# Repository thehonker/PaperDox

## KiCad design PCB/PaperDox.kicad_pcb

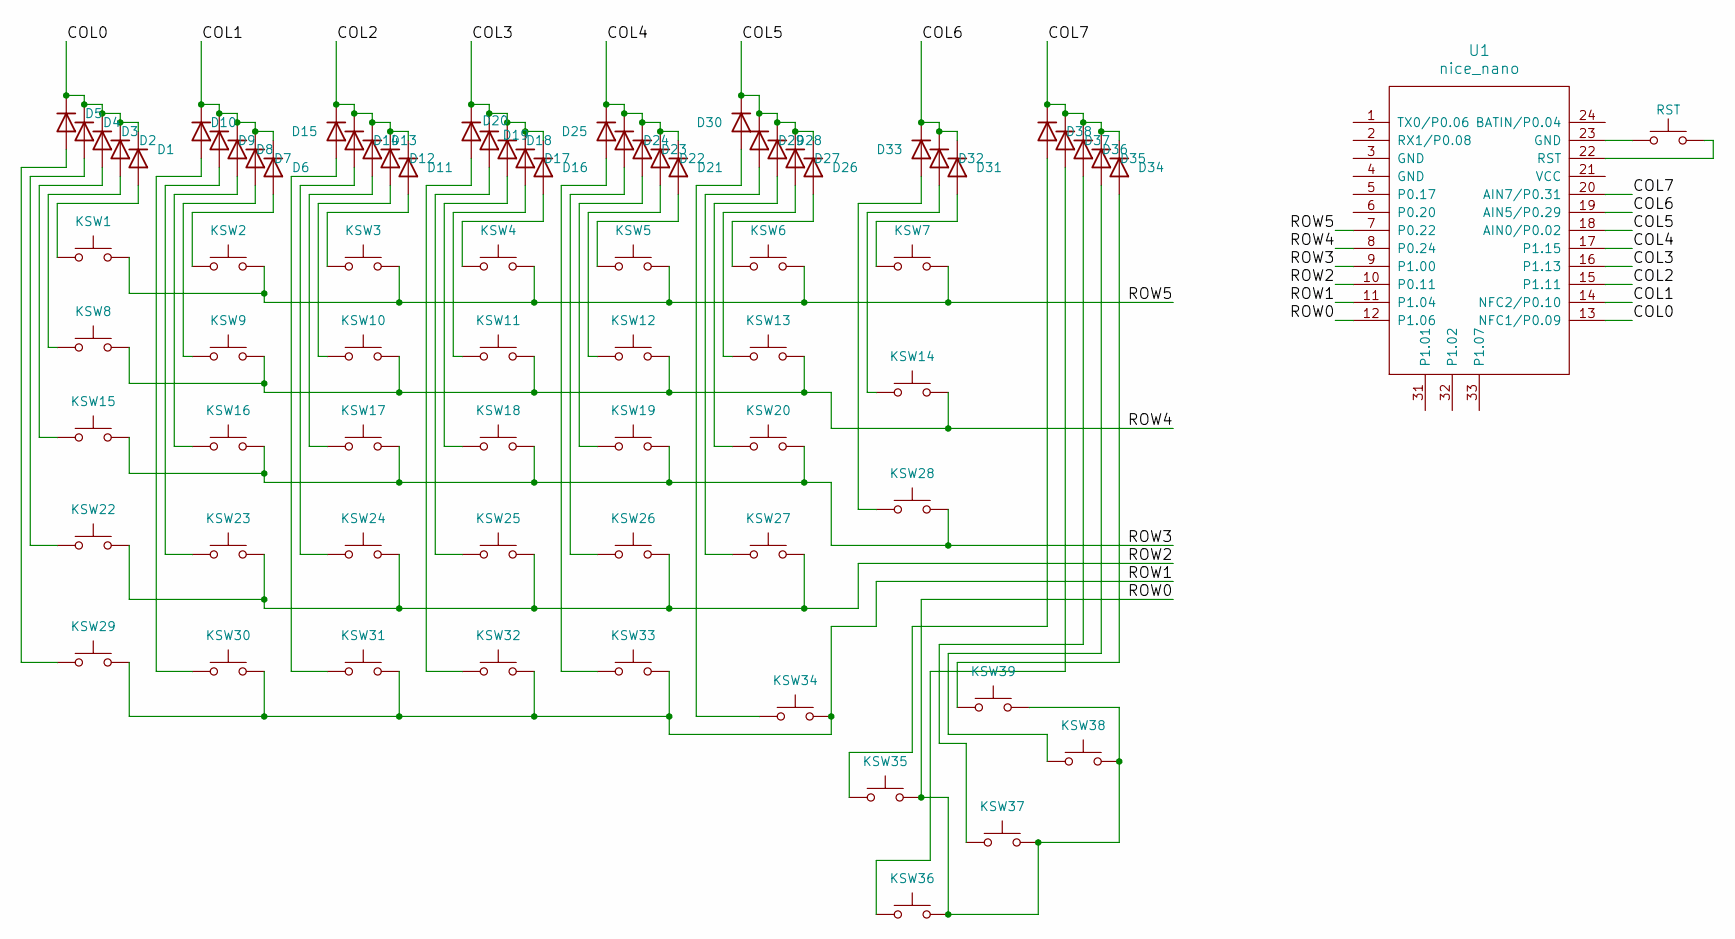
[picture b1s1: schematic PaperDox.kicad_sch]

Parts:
D1, D2, D3, D4, D5, D6, D7, D8, D9, D10, D11, D12, D13, D14, D15, D16, D17, D18, D19, D20, D21, D22, D23, D24, D25, D26, D27, D28, D29, D30, D31, D32, D33, D34, D35, D36, D37, D38: 1N4148; ComboDiode
KSW1, KSW2, KSW3, KSW4, KSW5, KSW6, KSW7, KSW8, KSW9, KSW10, KSW11, KSW12, KSW13, KSW14, KSW15, KSW16, KSW17, KSW18, KSW19, KSW20, KSW22, KSW23, KSW24, KSW25, KSW26, KSW27, KSW28, KSW29, KSW30, KSW31, KSW32, KSW33, KSW34, KSW35, KSW36, KSW37, KSW38, KSW39: Keyswitch; Choc_Hotswap
RST: SW_Push; SW_PUSH_6mm
U1: nice_nano; ProMicro_Mill-Max

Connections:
/COL0: D1.1 (K), D2.1 (K), D3.1 (K), D4.1 (K), D5.1 (K), U1.13 (NFC1/P0.09)
/COL1: D6.1 (K), D7.1 (K), D8.1 (K), D9.1 (K), D10.1 (K), U1.14 (NFC2/P0.10)
/COL2: D11.1 (K), D12.1 (K), D13.1 (K), D14.1 (K), D15.1 (K), U1.15 (P1.11)
/COL3: D16.1 (K), D17.1 (K), D18.1 (K), D19.1 (K), D20.1 (K), U1.16 (P1.13)
/COL4: D21.1 (K), D22.1 (K), D23.1 (K), D24.1 (K), D25.1 (K), U1.17 (P1.15)
/COL5: D26.1 (K), D27.1 (K), D28.1 (K), D29.1 (K), D30.1 (K), U1.18 (AIN0/P0.02)
/COL6: D31.1 (K), D32.1 (K), D33.1 (K), U1.19 (AIN5/P0.29)
/COL7: D34.1 (K), D35.1 (K), D36.1 (K), D37.1 (K), D38.1 (K), U1.20 (AIN7/P0.31); also elsewhere on the board
/ROW0: KSW35.2, KSW36.2, KSW37.2, KSW38.2, KSW39.2, U1.12 (P1.06)
/ROW1: KSW29.2, KSW30.2, KSW31.2, KSW32.2, KSW33.2, KSW34.2, U1.11 (P1.04)
/ROW2: KSW22.2, KSW23.2, KSW24.2, KSW25.2, KSW26.2, KSW27.2, U1.10 (P0.11)
/ROW3: KSW15.2, KSW16.2, KSW17.2, KSW18.2, KSW19.2, KSW20.2, KSW28.2, U1.9 (P1.00)
/ROW4: KSW8.2, KSW9.2, KSW10.2, KSW11.2, KSW12.2, KSW13.2, KSW14.2, U1.8 (P0.24)
/ROW5: KSW1.2, KSW2.2, KSW3.2, KSW4.2, KSW5.2, KSW6.2, KSW7.2, U1.7 (P0.22)
unnamed: D1.2 (A), KSW1.1
unnamed: D2.2 (A), KSW8.1
unnamed: D3.2 (A), KSW15.1
unnamed: D4.2 (A), KSW22.1
unnamed: D5.2 (A), KSW29.1
unnamed: D6.2 (A), KSW2.1
unnamed: D7.2 (A), KSW9.1
unnamed: D8.2 (A), KSW16.1
unnamed: D9.2 (A), KSW23.1
unnamed: D10.2 (A), KSW30.1
unnamed: D11.2 (A), KSW3.1
unnamed: D12.2 (A), KSW10.1
unnamed: D13.2 (A), KSW17.1
unnamed: D14.2 (A), KSW24.1
unnamed: D15.2 (A), KSW31.1
unnamed: D16.2 (A), KSW4.1
unnamed: D17.2 (A), KSW11.1
unnamed: D18.2 (A), KSW18.1
unnamed: D19.2 (A), KSW25.1
unnamed: D20.2 (A), KSW32.1
unnamed: D21.2 (A), KSW5.1
unnamed: D22.2 (A), KSW12.1
unnamed: D23.2 (A), KSW19.1
unnamed: D24.2 (A), KSW26.1
unnamed: D25.2 (A), KSW33.1
unnamed: D26.2 (A), KSW6.1
unnamed: D27.2 (A), KSW13.1
unnamed: D28.2 (A), KSW20.1
unnamed: D29.2 (A), KSW27.1
unnamed: D30.2 (A), KSW34.1
unnamed: D31.2 (A), KSW7.1
unnamed: D32.2 (A), KSW14.1
unnamed: D33.2 (A), KSW28.1
unnamed: D34.2 (A), KSW39.1
unnamed: D35.2 (A), KSW38.1
unnamed: D36.2 (A), KSW37.1
unnamed 50: RST.1, U1.23 (GND); also elsewhere on the board
unnamed 51: RST.2, U1.22 (RST); also elsewhere on the board

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
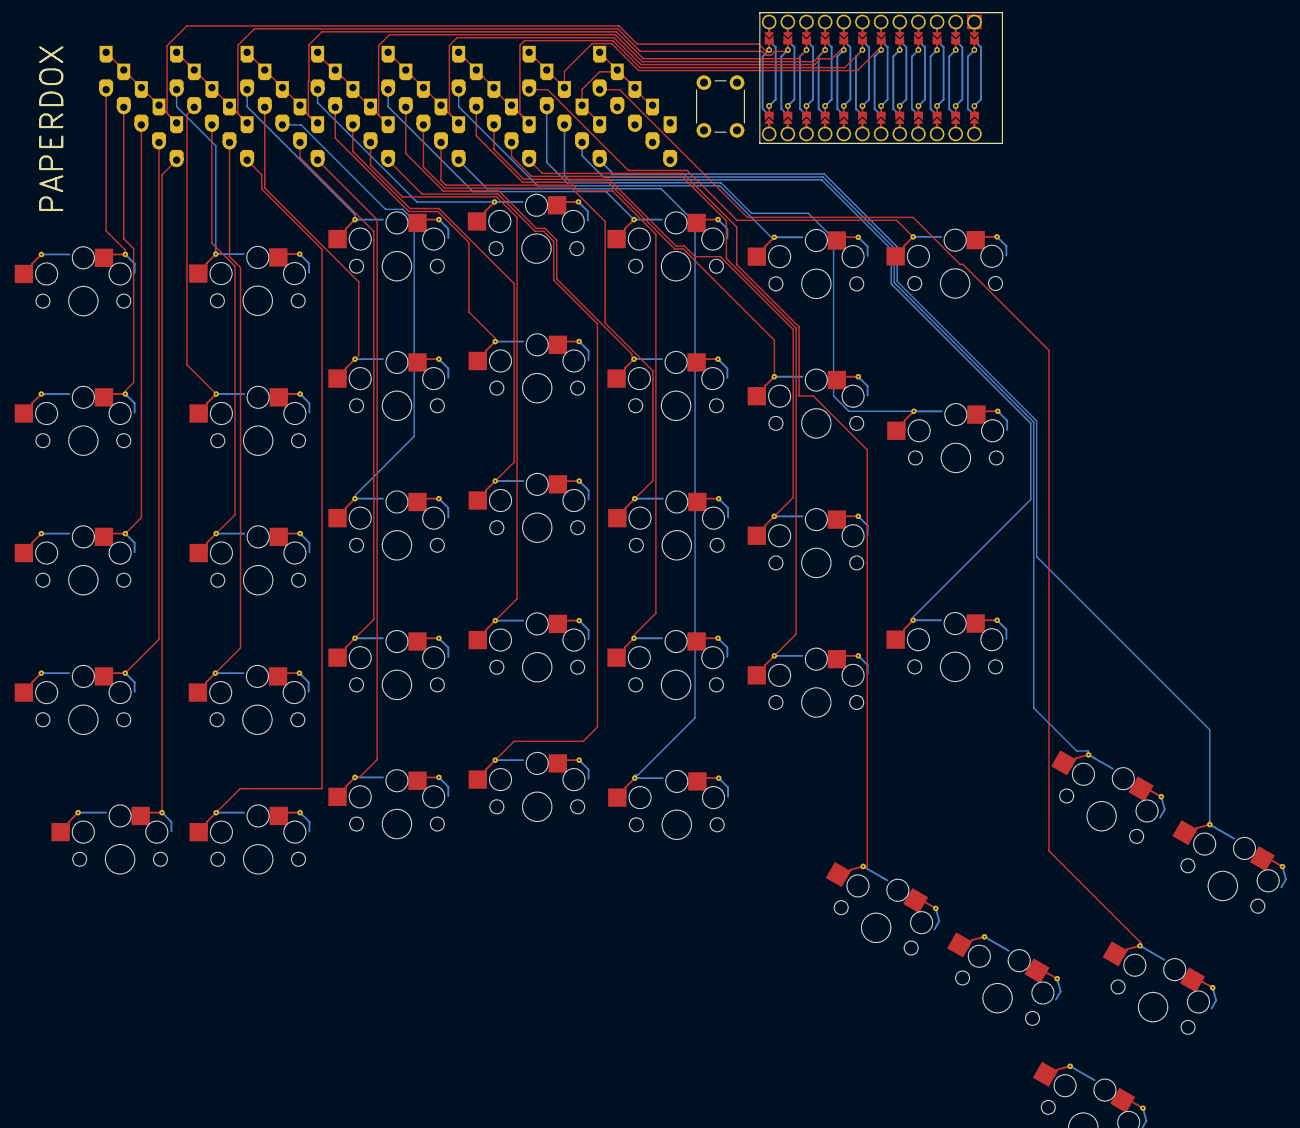
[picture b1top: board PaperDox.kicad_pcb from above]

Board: 2 copper layers, 80 parts (0 on the bottom side), 54 nets.

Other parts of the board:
D39, D40: 1N4148; ComboDiode
RST1: SW_Push; SW_PUSH_6mm

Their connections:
/COL7: D39.1 (K); also elsewhere on the board
unnamed 50: RST1.1; also elsewhere on the board
unnamed 51: RST1.2; also elsewhere on the board

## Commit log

2025-12-26 initial work on paperdox design
2026-01-04 i should commit and push this huh
2026-01-19 some wip
